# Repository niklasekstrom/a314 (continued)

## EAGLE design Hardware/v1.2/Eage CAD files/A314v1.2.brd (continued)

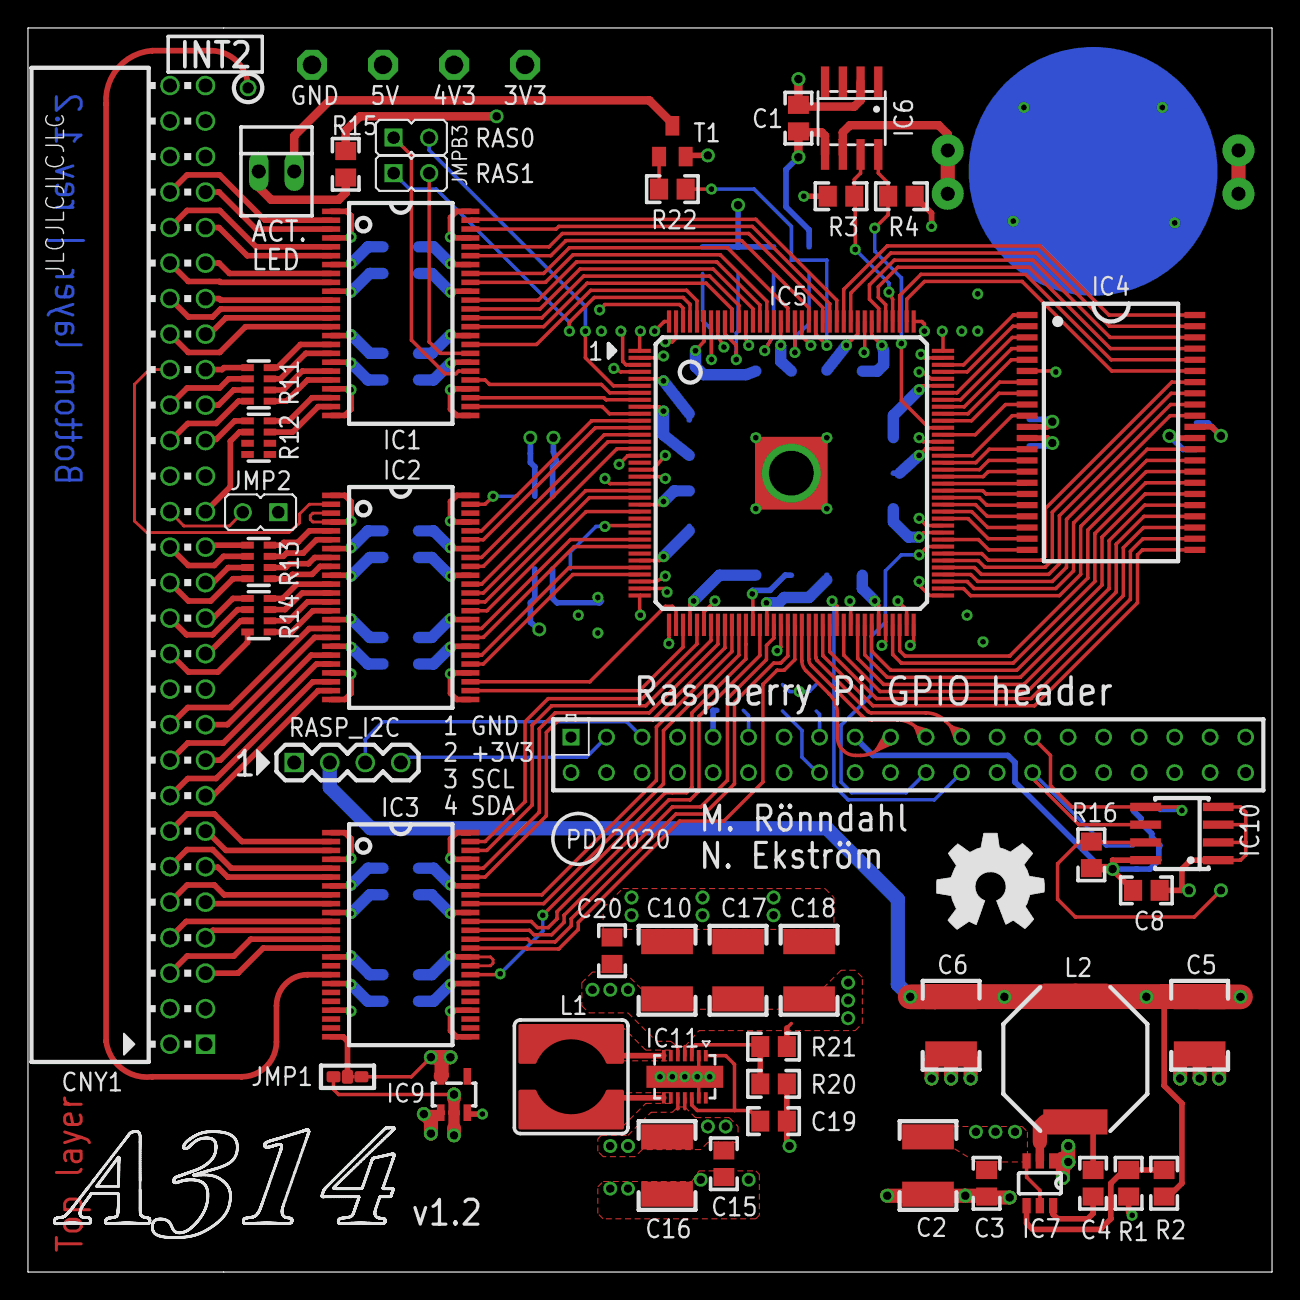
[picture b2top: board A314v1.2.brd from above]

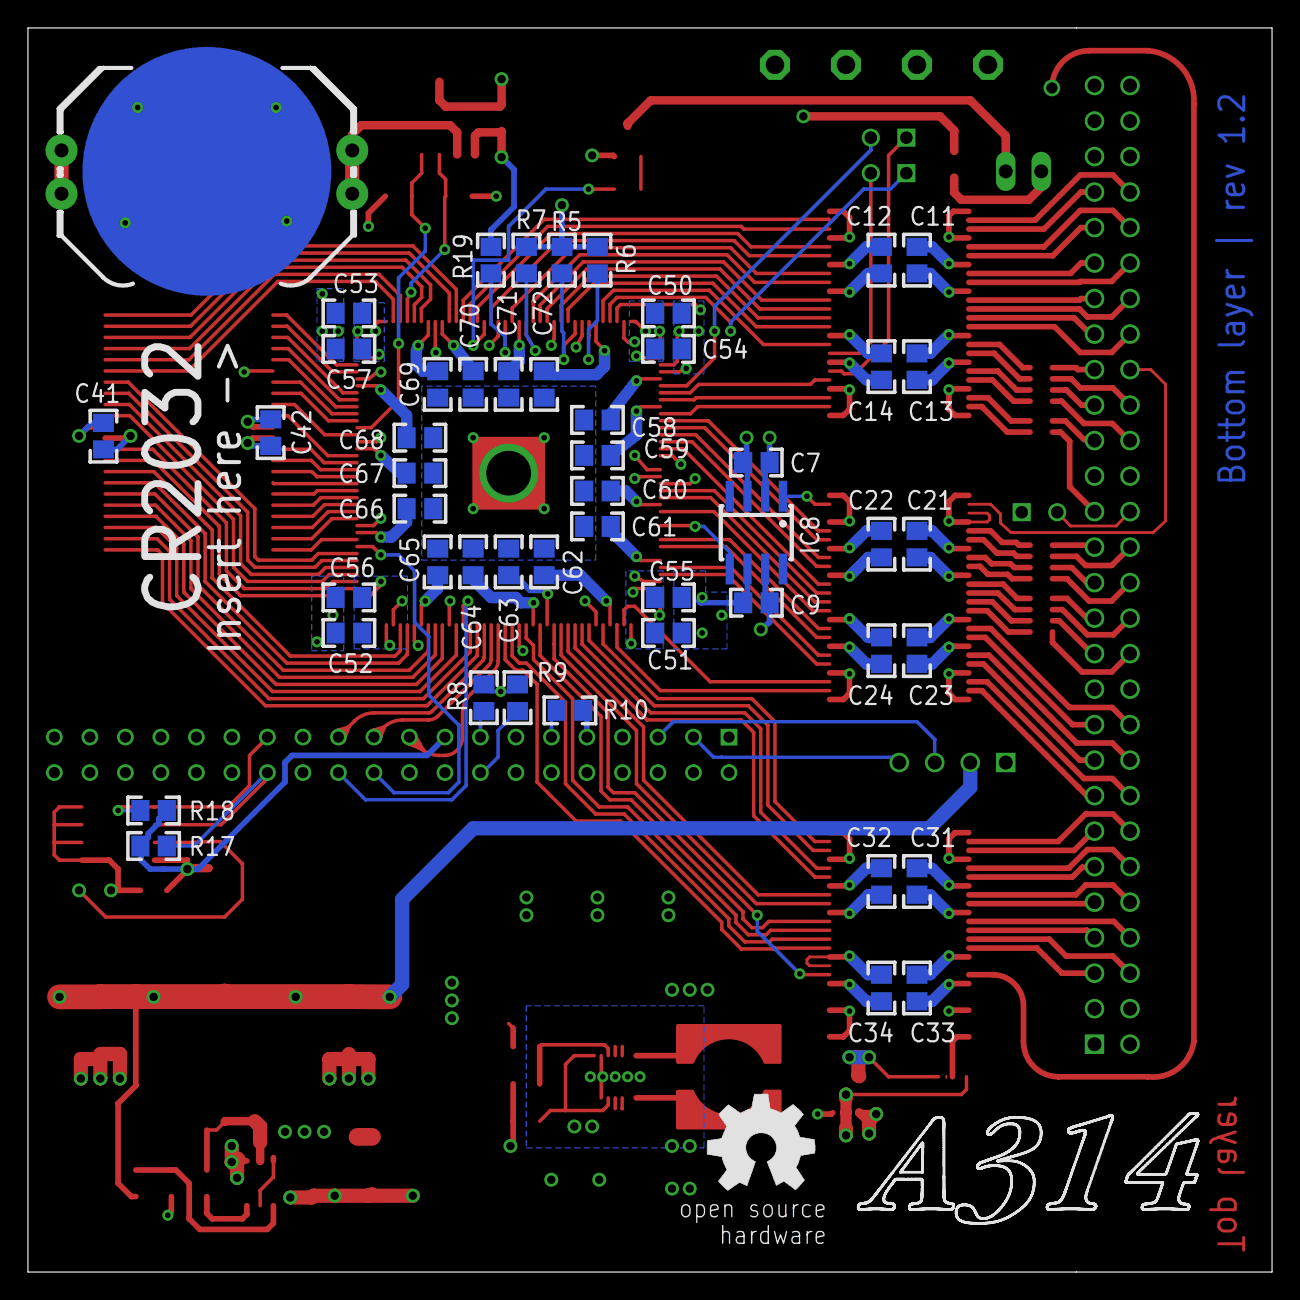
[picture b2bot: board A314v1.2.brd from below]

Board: 4 copper layers, 89.0 x 89.0 mm, 107 parts (53 on the bottom side), 180 nets.

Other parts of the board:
U$1: OSHW_8_NOTEXT
U$2, U$3: A314_LOGO
U$4: OSHW_8MM

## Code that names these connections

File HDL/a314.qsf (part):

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set_location_assignment PIN_61 -to RPI_SCE0
set_location_assignment PIN_58 -to RPI_SCLK0
#
set_location_assignment PIN_80 -to RPI_IRQ
#
set_location_assignment PIN_97 -to RTC_SCL
set_location_assignment PIN_112 -to RTC_SDA
#
set_location_assignment PIN_106 -to SR_A[0]
set_location_assignment PIN_105 -to SR_A[1]
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
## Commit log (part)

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2019-03-19 Initial commit.
2019-03-20 Initial commit of hardware related files
2019-03-27 Running pi without any arguments now starts a bash shell. Added support for resizing console window, which is propagated to the pseudo-tty.
2019-03-30 Removed pishell, in favour of the pi command which is more general.
2019-03-31 Added support in driver for INT2 interrupt handling. The idea is that this should lead to lower latency than using periodic polling using the VERTB interrupt.
2019-04-02 a314fs is now notified of a response using a message that is sent through R2A, instead of polling.
2019-04-12 Had forgotten to make pointer to CMEM registers volatile, which mattered when I turned on compiler optimizations in a previous commit.
2019-04-19 Trying to fix the horizontal alignment of an image.
2019-04-19 Updated README.
2019-04-20 Few clarifications and more pictures
2019-04-20 Fixed a314fs bug that prevented renaming directories.
2019-04-21 Added comments to source code files naming the author.
2019-04-22 Fixed order of requests to console handler. Don't request resize event notification until after received first window bounds report. Also slightly better error handling.
2019-04-23 Added CC0 license.
2019-05-12 Updated pi binary to go with updated pi.c a few commits back.
2019-05-13 Updated files to Quartus Prime Lite 18.1.
2019-07-18 Updated README.md with information about PiAudio.
2019-08-15 Added dockerfile/makefile and readme.md
2019-08-17 Added missing positional argument
    Also fixed remotewb.py so that it can be started standalone and not by a314d.
2019-08-17 Support for A500+.
    These changes let A314 work in an A500+, providing an additional 1MB of chip ram for a total of 2MB chip.
    The SPI protocol had to be modified so that addresses are sent as 20 bits instead of 19 bits, so that the entire 1MB of SRAM can be addressed.
    The GetA314MemBase() API function exposed by a314.device was replaced with a more general TranslateAddressA314() function. All applications that previously used GetA314MemBase() had to be updated. Th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
    At this time a small change needs to be made in HDL/a314_top.v at line 107, and the Verilog then needs to be recompiled and written to the FPGA, in order to use A314 in an A500+. The reason is that w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
2019-09-19 Added information about #a314 IRC channel.
2019-09-25 PCB Update (1.1) that addresses issues #10 and #11
    This is a minor update that will allow for a single firmware to serve all A500 motherboards up to rev.8.
    A500+ owners will get an additional 1MB of chipram, previous boards (up to rev.6) will use ½MB.
2019-10-05 Added Makefile that builds software
    The rpi_docker_build.sh script uses a public docker image containing vbcc
    to build all software to Software/bin using the makefile on a Raspberry Pi.
    To use the script, docker must first be installed on the RPi.
    sudo make install copies all RPi files into the appropriate directories.
    After that, the a314d daemon is enabled using:
    sudo systemctl daemon-reload
2019-11-09 Added note to follow wiki instructions
2020-02-02 Added building diag to Makefile
2020-02-13 Handle dates before Amiga epoch
    Dates before Amiga epoc 1978 becomes negative and crashes struct.pack.
    Guard to make sure that days can be represented as unsigned int.
2020-02-22 Refactored a314.device
    Refactored a314.device by grouping related procedures and moving them to new
    source code files.
    No functional changes were made.
2020-02-22 Added routine to create sockets
2020-02-22 Added constant for CMEM configuration nibble
2020-02-22 Move setting up interrupts to task_start()
2020-02-22 Refactored app message handlers
2020-02-22 Refactor handling of received packets
2020-02-22 Converted picmd.py to Python 3
    The picmd.py program now runs on Python 3 instead of as previously on Python 2.
    The goal of issue #31 is to convert all Python code to Python 3.
2020-02-23 Converted a314fs.py to Python 3
    All Python code in the repo is now using Python 3. This closes #31.
2020-03-10 Added versioning to firmware
2020-03-10 Maintain memory mappings for each 512kB bank
2020-04-12 Fix a314fs build script for Python 3 in Windows
2020-04-13 Forgot to add bin/remote-mouse as a make target
2020-05-13 Added execute permission for build script
2020-06-30 Update A314-500 v1.2 BOM.pdf
    Correction of resistor amount
2020-07-25 Use SIGF_SINGLE instead of allocating signal
2020-07-28 Added depencencies for Raspian Lite
    The build process does not require depencencies that do not come installed by default on Raspbian Lite.
2020-08-07 Unused RegA slots return zero
    Previously any unused RegA slot would return the firmware version number.
    This should have been harmless since before reading a RegA slot other than the
    version number the driver should read the firmware version number to figure out
    if a particular slot is implemented or not.
    Nevertheless, with this change, reading from an unused slot returns zero.
2020-08-20 Added support for A314-600 to master branch
    Previously there was a separate branch for the A600 version of A314, but this
    functionality has now been merged into the master branch.
    A new revision, a314_600, has been added to the Quartus project.
    A macro, is_a600, is used to control the compilation in a few places, mostly in
    the top entity a314_top.v.
    A new SPI protocol command has been added, SPI_PROTOCOL_VERSION. On older HDL
2020-10-24 Fix bug with directory iteration and file deletion in a314fs
    ACTION_EXAMINE_OBJECT and _NEXT didn't work correctly when deleting a
    directory with several files, leaving files and because of that being
    unable to delete the directory.
2020-10-25 Allow rename with same source and destination file in a314fs
    Renaming a file to itself is allowed in AmigaDOS, so if the source and
    destination paths are identical reply with success. Fixes #54
2020-11-18 Add ACTION_DISK_INFO and ACTION_INFO to a314fs
    This update replaces the placeholder values for ACTION_DISK_INFO and ACTION_INFO with actual values from the Raspberry OS.
    The values are then used by the Amiga OS to convey the amount of free and used space on the PiDisk device.
2020-12-30 Add support for comments and file/directory metadata
    Amiga metadata that can not be mapped to any Linux equivalent can be
    stored in a metadata file. Using a colon (:), an illegal filename
    character on the Amiga, in the metadata filename assures that there
    can be no collisions with any Amiga files.
    The metadata file will only be created if the metadata changes from
    the default.
2020-12-30 Enforce read, write and delete protection
    Effort has been made to make sure any protection works identical to
    how the Fast File System behaves.
2021-01-06 Add minor refactorings
2021-01-18 Add FLIP_DONE event
2021-03-09 Update description of SANA-II driver
2021-05-09 Removed global variables in device.c
2021-05-09 Removed global variables from startup
2021-05-09 Remove global variable from a314driver
2021-05-12 Add a314disk.device virtual floppy drive driver
    The a314disk.device lets you mount ADF files that are stored on the
    Raspberry Pi as disks in drives PD0: to PD3:.
    The a314disk.device is ROMable, meaning that it can be added to the
    kickstart ROM image and the Amiga can then boot off of the boot block
    on the disk inserted in one of those drives.
2021-05-15 Add building of a314disk.device to build script
2021-07-21 Move a314d.py to a314d directory
    Also remove the script rasp-com.py as it was never used.
2021-07-21 Change owner for files in bin folder to pi
    When the rpi_docker_build.sh script is run it creates a bin folder
    where all built files go. When those files are created they have root
    as owner. The change in this commit will set the owner of those files
    to be the pi user.
2021-08-13 Improved error checking in a314fs rename_object
    This fixes #55 by interpreting a Python OSError as an object in use
    error.
2021-12-10 more details about install
2022-06-20 Add config file for programming FPGA using openocd
2022-07-28 Add support for Amiga clockport interface
    These changes are meant to work with this interface:
    https://github.com/niklasekstrom/clockport_pi_interface
2022-08-11 Remove hardcoded peripheral base and size constants
    Different models of Raspberry Pi have the memory mapped registers that
    controls peripherals (such as GPIO) at different addresses.
    This change uses the official method to find those base and size
    values, instead of hardcoding them.
2022-09-16 Make dependency on python3-pip explicit
2022-09-26 Update build instructions
    Fixes #73.
2022-10-04 Fix some formatting mistakes
2022-11-27 WiP: picmd (with a314.device) works, but a314drive.device does not compile ... yet with NDK32
2022-12-10 Move all adapter specific code to cp_pi_if
2022-12-10 Pass pointer to A314Device to adapter procedures
2022-12-25 Refactored the a314d Python module as a class
    Also refactored the disk service as it used the a314d module.
    While doing it, also refactored the disk service as a class.
2023-01-05 Add constant for invalid A314 address
    Previously AllocMemA314 returned 0 on failure, but now that changed
    to return -1 instead. Technically this is a breaking API change,
    but hopefully it doesn't cause any issues.
    In any case, if someone is updating a314.device then the other binaries
    should typically be recompiled too.
2023-01-17 Add step in instructions to enable ip forwarding
2023-01-19 Send start message as data instead of in shared mem
2023-01-19 Refactor pi startup error handling
2023-01-20 Restore priority when PiAudio terminates
2023-03-05 Update A314 installation to be user agnostic
    Can no longer count on there being a default 'pi' user to use in
    various hardcoded paths in A314. Update makefile to substitute with
    the installing users home directory etc.
2023-03-07 Add support for scroll wheel mouse events
    Contributed by HeathenUK from the Discord server.
2023-03-09 Add systemd service files for td and cp variants
2023-04-04 Add dist make target to build installation packages
    Using the dist target, a self-extracting and installing package can be
    built. This package can then be distributed to end user for a very
    easy installation. The installation script installs the A314 binaries
    and any support files. It can also optionally install dependencies and
    perform necessary changes to configuration files in /boot.
2023-07-21 Make changes necessary to compile using NDK3.2
2023-08-27 Update gitignore
2023-09-10 Add list of addresses to probe for FE board
2023-10-01 Update README.md with information about config file
2023-11-07 Add iptables to list of dependencies
2023-12-09 Make minor change to ethernet install instructions
2023-12-16 Fix warnings when building and installing bpls2gif
2024-05-19 Use gpio device rather than deprecated sysfs
2024-05-20 Add define needed for Python >= 3.10
2024-05-28 Add initial version of libremote
    Includes a simple example library, and a client for that library.
2024-05-28 Update build scripts
2024-05-29 Set library version to 3.0
    The version for bsdsocket.library must be at least 3 to work.
2024-05-29 Add enough functions to run wget
2024-05-30 Add ability for signal to interrupt connect
2024-06-03 Add more uniform naming of libremote files
2024-08-13 Fix MyCreatePort to free allocated resources
    In some cases, the allocated resources (e.g., signal bits)
    are not properly freed before returning, which could lead to resource leaks.
    It's better to consistently free any allocated resources before returning in
    case of an error.
    These modifications ensure that any allocated resources are properly cleaned
    up in case of an error, preventing resource leaks.
2024-08-24 Split hardware/hdl design files to separate repos
2024-10-26 Add check to only consider memory below 16 MB
    Only consider memory below 16 MB to be A314 shared memory.
2024-12-08 Add ifupdown package to list of dependencies
2025-05-24 Add images of the hardware variants to README
2025-06-18 add gayle adapter clockport support (suggested changes by Niklas)
2025-07-07 Remove dependency on bcm_host library
2025-08-03 Move flashing to its own script
